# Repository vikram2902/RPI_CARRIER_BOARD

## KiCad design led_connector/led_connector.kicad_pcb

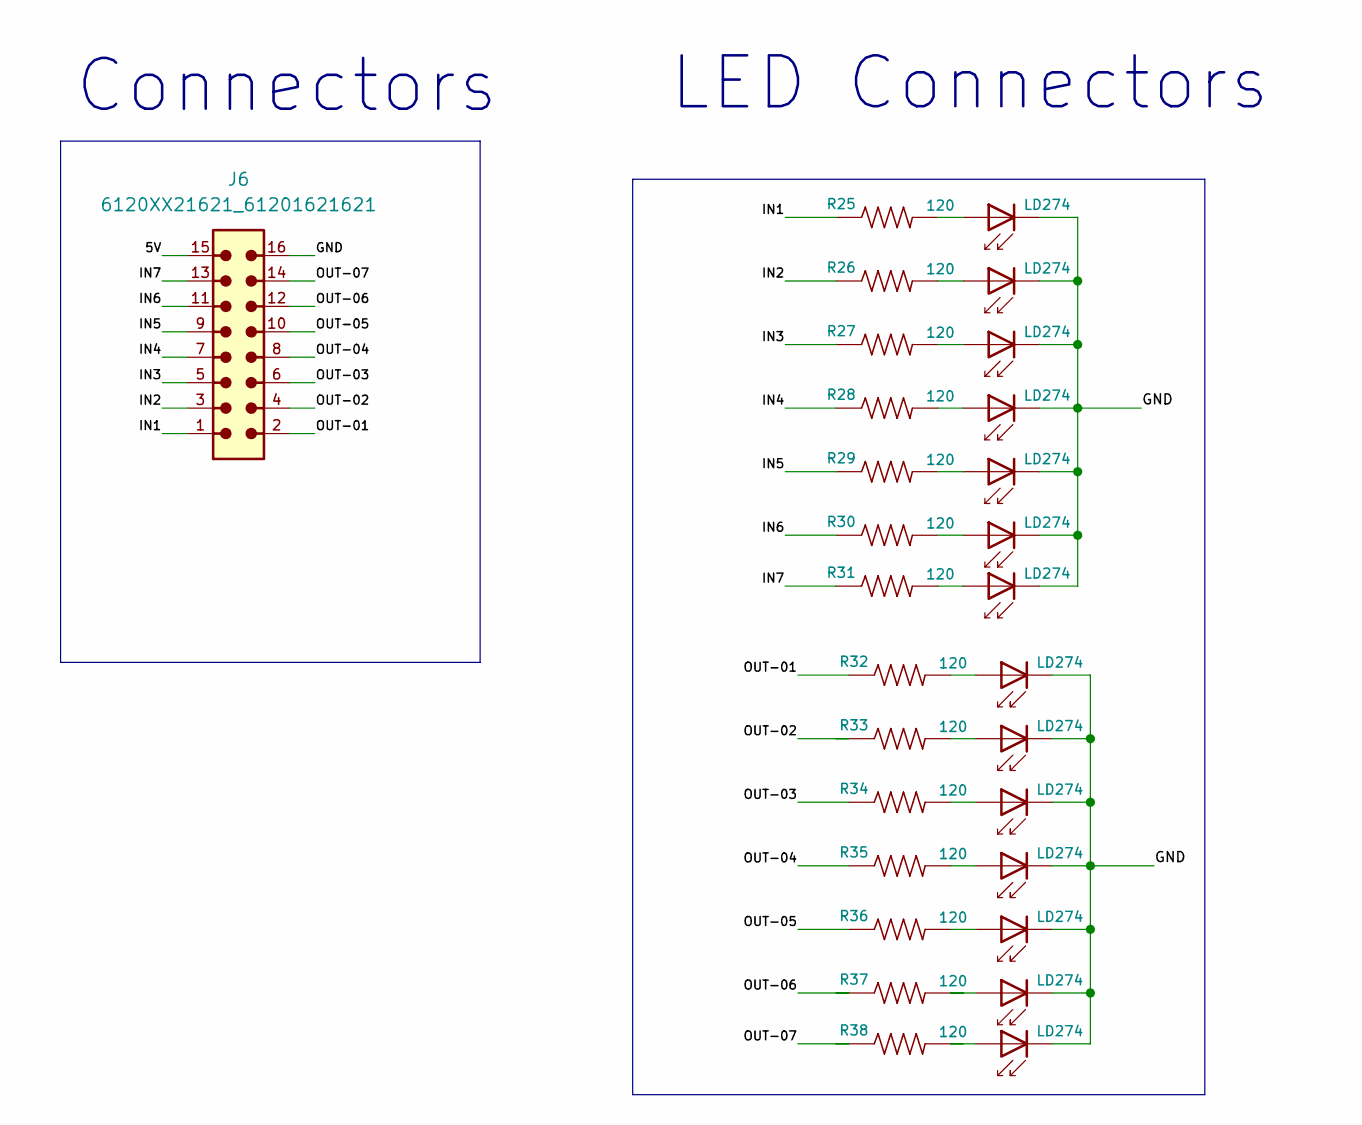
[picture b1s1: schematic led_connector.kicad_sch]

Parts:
D1, D3, D4, D5, D6, D7, D8, D9, D10, D11, D12, D13, D14, D15: LD274; LED_D3.0mm
J6: 6120XX21621_61201621621; 61201621621
R25, R26, R27, R28, R29, R30, R31, R32, R33, R34, R35, R36, R37, R38: 120; 0805

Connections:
/5V: J6.15
/GND: D1.1 (K), D3.1 (K), D4.1 (K), D5.1 (K), D6.1 (K), D7.1 (K), D8.1 (K), D9.1 (K), D10.1 (K), D11.1 (K), D12.1 (K), D13.1 (K), D14.1 (K), D15.1 (K), J6.16
/IN1: J6.1, R25.1
/IN2: J6.3, R26.1
/IN3: J6.5, R27.1
/IN4: J6.7, R28.1
/IN5: J6.9, R29.1
/IN6: J6.11, R30.1
/IN7: J6.13, R31.1
/OUT-01: J6.2, R32.1
/OUT-02: J6.4, R33.1
/OUT-03: J6.6, R34.1
/OUT-04: J6.8, R35.1
/OUT-05: J6.10, R36.1
/OUT-06: J6.12, R37.1
/OUT-07: J6.14, R38.1
unnamed: D1.2 (A), R38.2
unnamed: D3.2 (A), R25.2
unnamed: D4.2 (A), R26.2
unnamed: D5.2 (A), R27.2
unnamed: D6.2 (A), R28.2
unnamed: D7.2 (A), R29.2
unnamed: D8.2 (A), R30.2
unnamed: D9.2 (A), R32.2
unnamed: D10.2 (A), R33.2
unnamed: D11.2 (A), R34.2
unnamed: D12.2 (A), R35.2
unnamed: D13.2 (A), R36.2
unnamed: D14.2 (A), R37.2
unnamed: D15.2 (A), R31.2

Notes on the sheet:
LED Connectors
Connectors

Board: 2 copper layers, 29 parts (0 on the bottom side), 29 nets, no tracks yet.

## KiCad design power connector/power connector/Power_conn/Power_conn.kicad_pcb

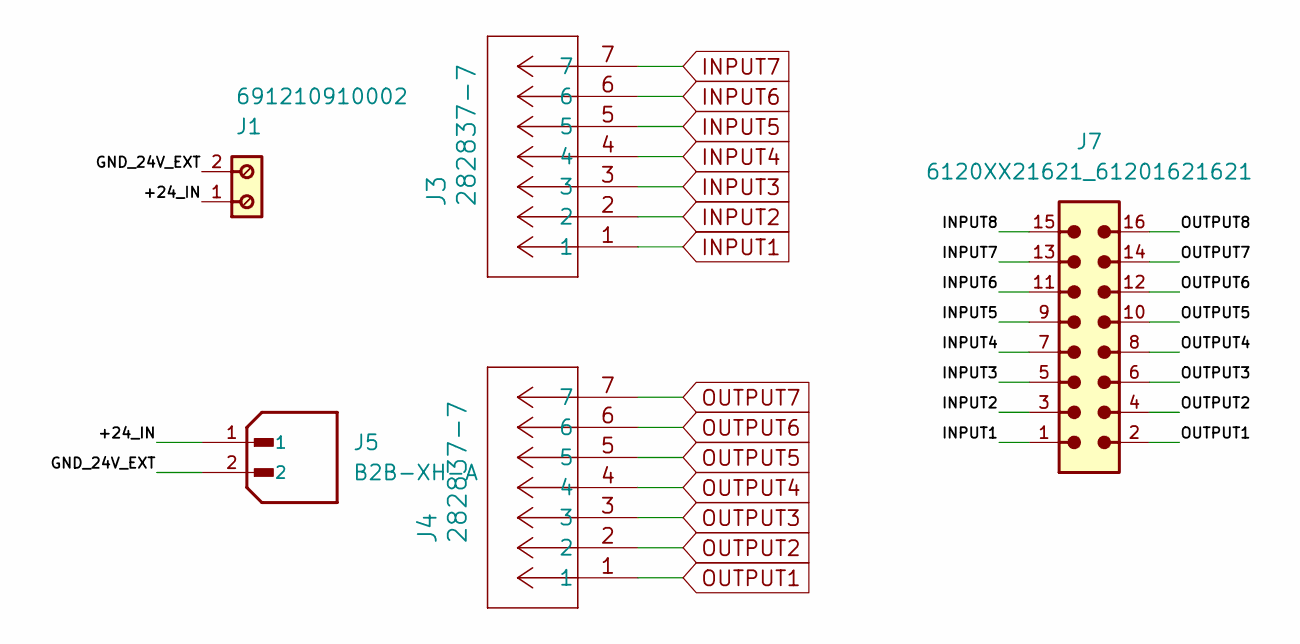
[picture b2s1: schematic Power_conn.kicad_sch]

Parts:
J1: 691210910002
J3, J4: 282837-7; 282837-7_TEC
J5: B2B-XH-A; JST_B2B-XH-A; PARTREV N/A
J7: 6120XX21621_61201621621; 61201621621

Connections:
/+24_IN: J1.1, J5.1
/GND_24V_EXT: J1.2, J5.2
/INPUT8: J7.15
/OUTPUT8: J7.16
INPUT1: J3.1, J7.1
INPUT2: J3.2, J7.3
INPUT3: J3.3, J7.5
INPUT4: J3.4, J7.7
INPUT5: J3.5, J7.9
INPUT6: J3.6, J7.11
INPUT7: J3.7, J7.13
OUTPUT1: J4.1, J7.2
OUTPUT2: J4.2, J7.4
OUTPUT3: J4.3, J7.6
OUTPUT4: J4.4, J7.8
OUTPUT5: J4.5, J7.10
OUTPUT6: J4.6, J7.12
OUTPUT7: J4.7, J7.14

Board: 2 copper layers, 5 parts (0 on the bottom side), 16 nets, no tracks yet.

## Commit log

2025-09-17 Replaced old repo with new carrier board files
2025-09-17 Upload new carrier board files
2025-09-17 Added carrier board project files
